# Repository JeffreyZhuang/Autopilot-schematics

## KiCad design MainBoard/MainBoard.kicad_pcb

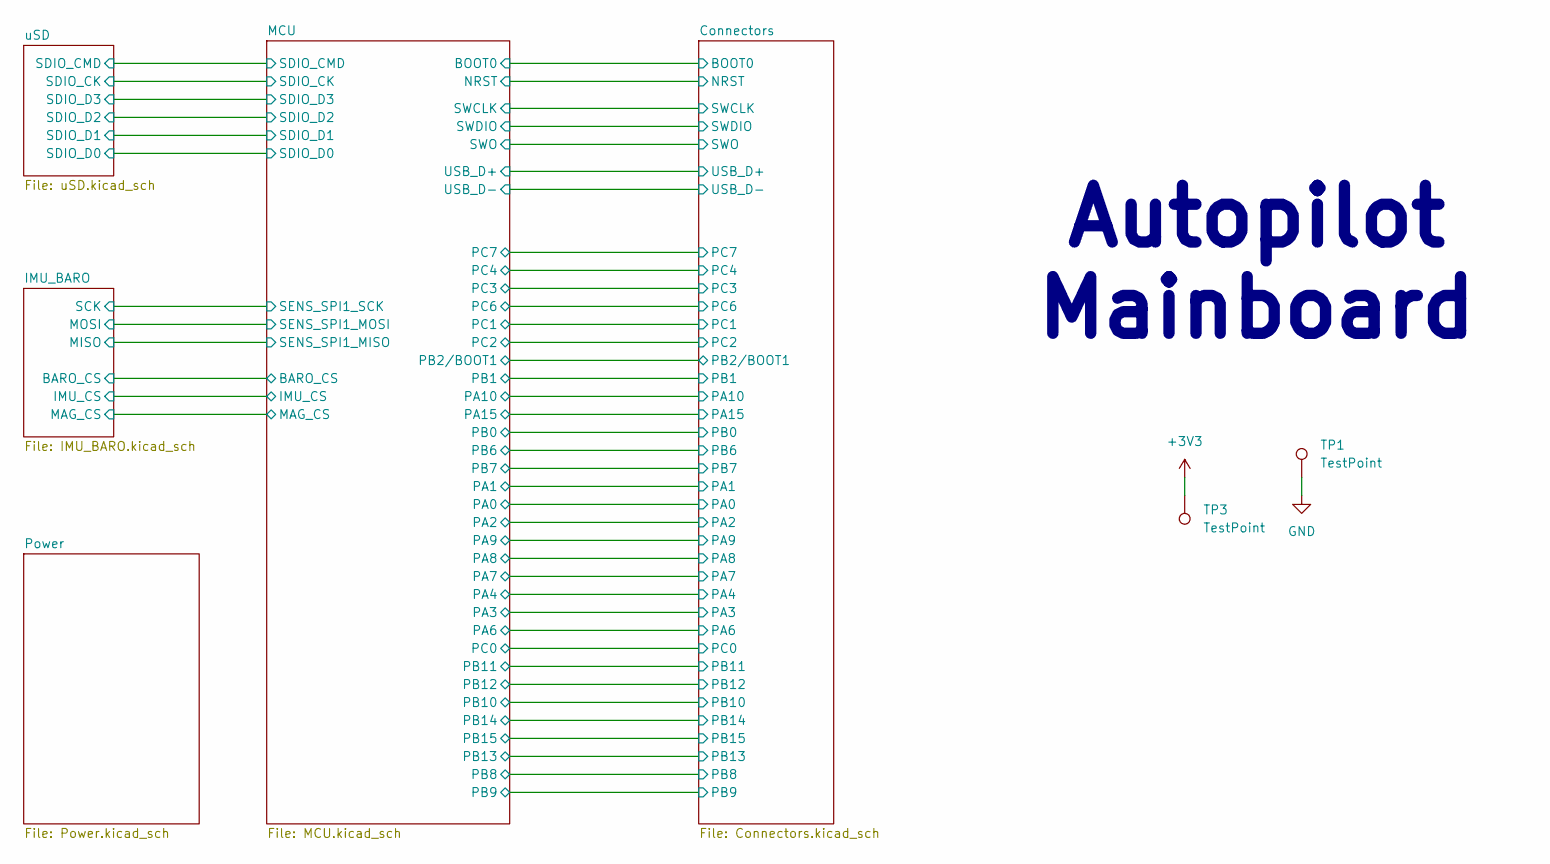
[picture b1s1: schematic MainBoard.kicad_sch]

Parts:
TP1: TestPoint; TestPoint_THTPad_D1.0mm_Drill0.5mm; LCSC Part # N/A
TP3: TestPoint; TestPoint_Pad_D1.0mm; LCSC Part # N/A

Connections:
+3V3: TP3.1; also elsewhere on the board
GND: TP1.1; also elsewhere on the board

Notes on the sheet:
Autopilot Mainboard

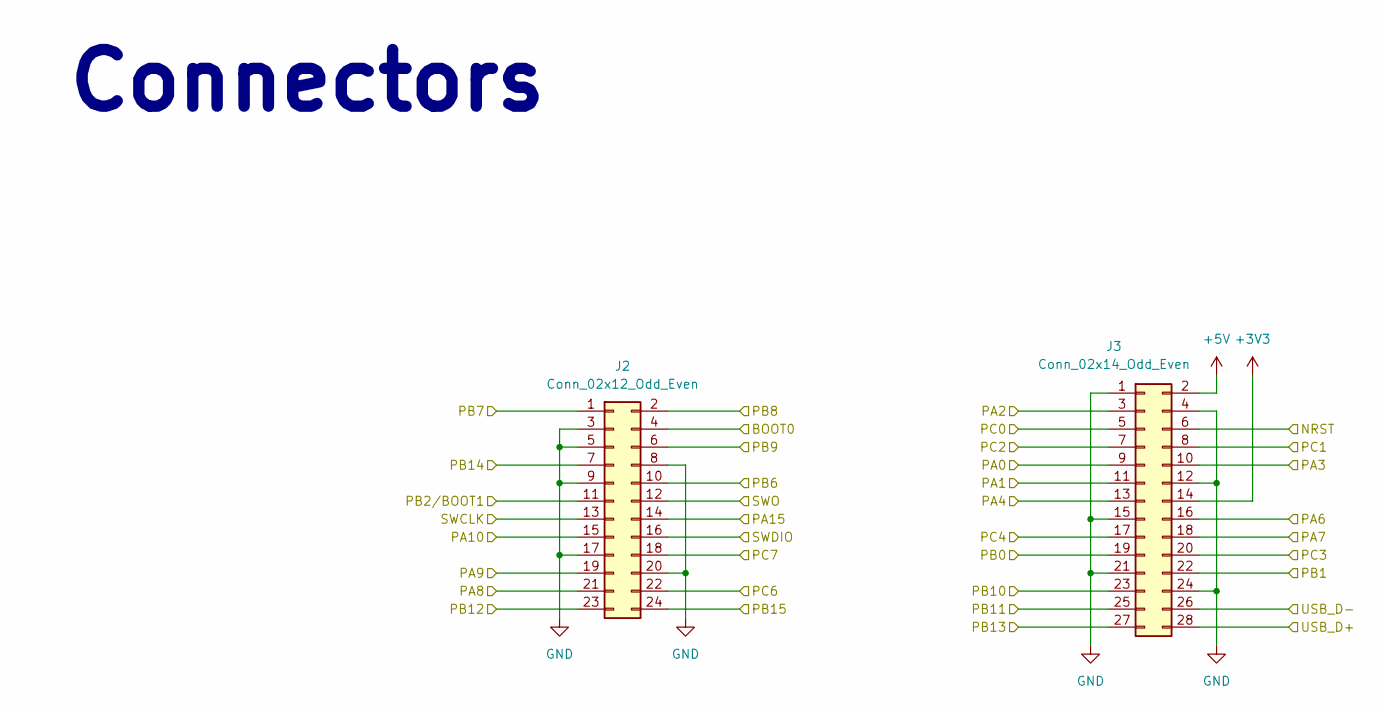
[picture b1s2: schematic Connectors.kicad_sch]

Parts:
J2: Conn_02x12_Odd_Even; PinHeader_2x12_P1.00mm_Vertical_SMD; LCSC Part # N/A
J3: Conn_02x14_Odd_Even; PinHeader_2x14_P1.00mm_Vertical_SMD; LCSC Part # N/A

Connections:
+3V3: J3.14; also elsewhere on the board
+5V: J3.2; also elsewhere on the board
/Connectors/BOOT0: J2.4; also elsewhere on the board
/Connectors/NRST: J3.6; also elsewhere on the board
/Connectors/PA0: J3.9; also elsewhere on the board
/Connectors/PA1: J3.11; also elsewhere on the board
/Connectors/PA2: J3.3; also elsewhere on the board
/Connectors/PA3: J3.10; also elsewhere on the board
/Connectors/PA4: J3.13; also elsewhere on the board
/Connectors/PA6: J3.16; also elsewhere on the board
/Connectors/PA7: J3.18; also elsewhere on the board
/Connectors/PA8: J2.21; also elsewhere on the board
/Connectors/PA9: J2.19; also elsewhere on the board
/Connectors/PA10: J2.15; also elsewhere on the board
/Connectors/PA15: J2.14; also elsewhere on the board
/Connectors/PB0: J3.19; also elsewhere on the board
/Connectors/PB1: J3.22; also elsewhere on the board
/Connectors/PB2/BOOT1: J2.11; also elsewhere on the board
/Connectors/PB6: J2.10; also elsewhere on the board
/Connectors/PB7: J2.1; also elsewhere on the board
/Connectors/PB8: J2.2; also elsewhere on the board
/Connectors/PB9: J2.6; also elsewhere on the board
/Connectors/PB10: J3.23; also elsewhere on the board
/Connectors/PB11: J3.25; also elsewhere on the board
/Connectors/PB12: J2.23; also elsewhere on the board
/Connectors/PB13: J3.27; also elsewhere on the board
/Connectors/PB14: J2.7; also elsewhere on the board
/Connectors/PB15: J2.24; also elsewhere on the board
/Connectors/PC0: J3.5; also elsewhere on the board
/Connectors/PC1: J3.8; also elsewhere on the board
/Connectors/PC2: J3.7; also elsewhere on the board
/Connectors/PC3: J3.20; also elsewhere on the board
/Connectors/PC4: J3.17; also elsewhere on the board
/Connectors/PC6: J2.22; also elsewhere on the board
/Connectors/PC7: J2.18; also elsewhere on the board
/Connectors/SWCLK: J2.13; also elsewhere on the board
/Connectors/SWDIO: J2.16; also elsewhere on the board
/Connectors/SWO: J2.12; also elsewhere on the board
/Connectors/USB_D+: J3.28; also elsewhere on the board
/Connectors/USB_D-: J3.26; also elsewhere on the board
GND: J2.3, J2.5, J2.8, J2.9, J2.17, J2.20, J3.1, J3.4, J3.12, J3.15, J3.21, J3.24; also elsewhere on the board

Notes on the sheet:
Connectors

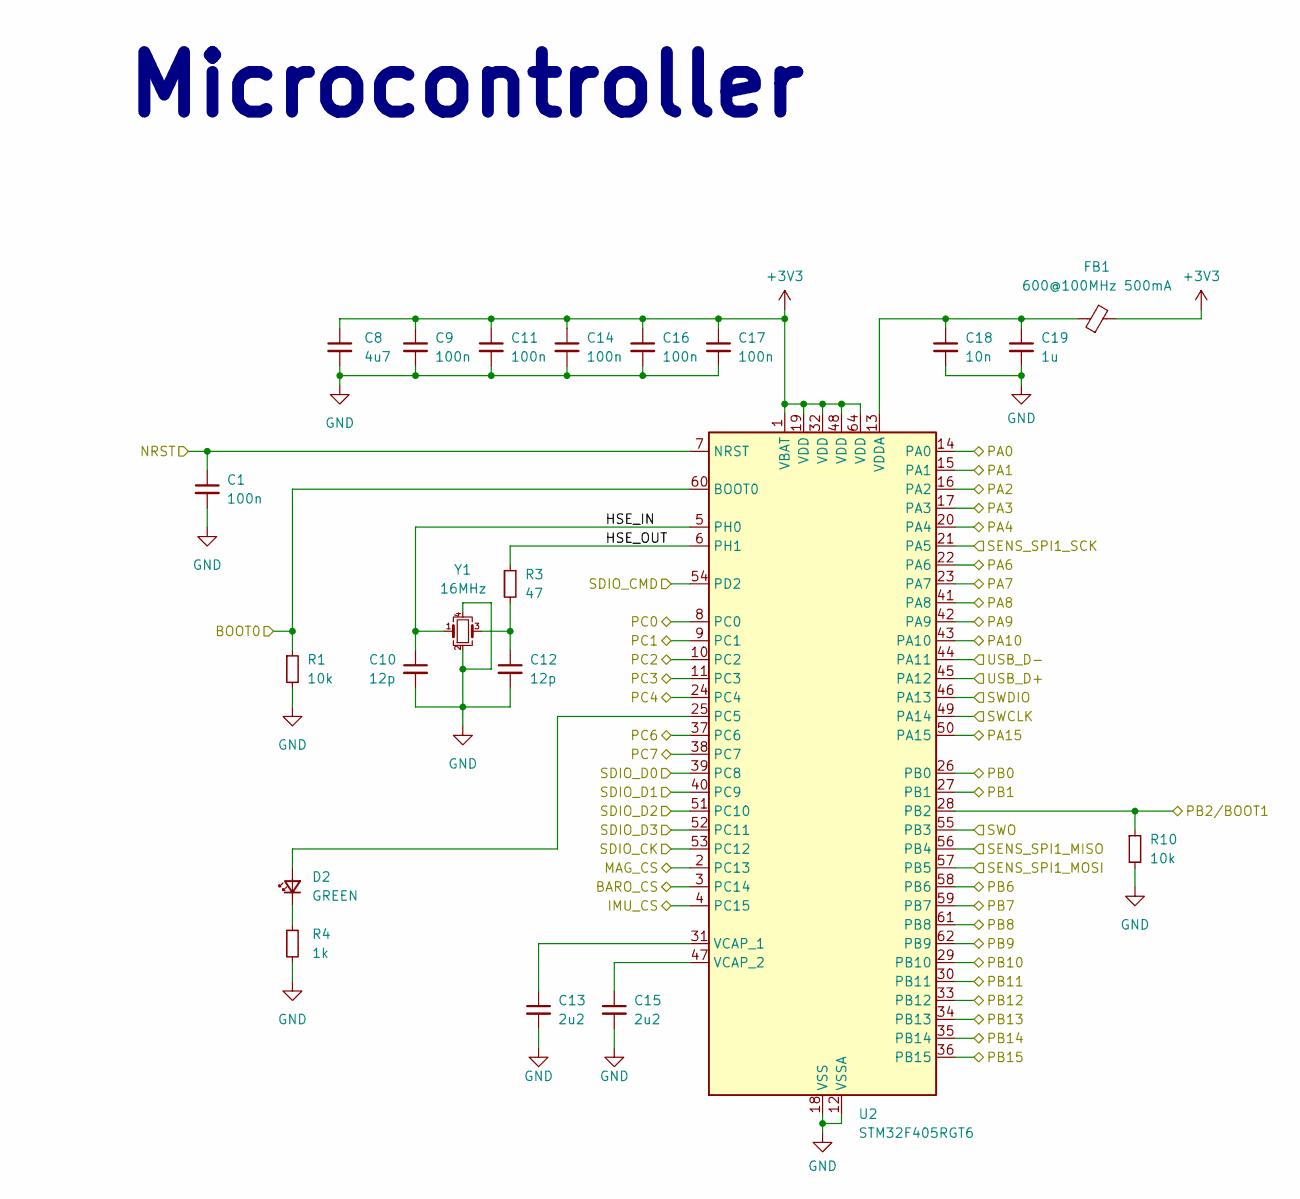
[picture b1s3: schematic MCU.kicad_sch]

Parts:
C1, C9, C11, C14, C16, C17: 100n; C_0402_1005Metric_Pad0.74x0.62mm_HandSolder; LCSC Part # N/A (C1525)
C8: 4u7; C_0402_1005Metric_Pad0.74x0.62mm_HandSolder; LCSC Part # N/A (C368809)
C10, C12: 12p; C_0402_1005Metric_Pad0.74x0.62mm_HandSolder; LCSC Part # N/A (C107034)
C13, C15: 2u2; C_0402_1005Metric_Pad0.74x0.62mm_HandSolder; LCSC Part # C170151
C18: 10n; C_0402_1005Metric_Pad0.74x0.62mm_HandSolder; LCSC Part # N/A (C15195)
C19: 1u; C_0402_1005Metric_Pad0.74x0.62mm_HandSolder; LCSC Part # N/A (C52923)
D2: GREEN; LED_0402_1005Metric_Pad0.77x0.64mm_HandSolder; LCSC Part # C130723
FB1: 600@100MHz 500mA; L_0805_2012Metric_Pad1.05x1.20mm_HandSolder; LCSC Part # N/A (C1017)
R1, R10: 10k; R_0402_1005Metric_Pad0.72x0.64mm_HandSolder; LCSC Part # N/A (C25744)
R3: 47; R_0402_1005Metric_Pad0.72x0.64mm_HandSolder; LCSC Part # N/A (C25118)
R4: 1k; R_0402_1005Metric_Pad0.72x0.64mm_HandSolder; LCSC Part # N/A (C11702)
U2: STM32F405RGT6; LQFP-64_10x10mm_P0.5mm; LCSC Part # C15742
Y1: 16MHz; Crystal_SMD_3225-4Pin_3.2x2.5mm; LCSC Part # N/A (C13738)

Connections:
+3V3: C8.1, C9.1, C11.1, C14.1, C16.1, C17.1, FB1.2, U2.1 (VBAT), U2.19 (VDD), U2.32 (VDD), U2.48 (VDD), U2.64 (VDD); also elsewhere on the board
/Connectors/BOOT0: R1.1, U2.60 (BOOT0); also elsewhere on the board
/Connectors/NRST: C1.1, U2.7 (NRST); also elsewhere on the board
/Connectors/PA0: U2.14 (PA0); also elsewhere on the board
/Connectors/PA1: U2.15 (PA1); also elsewhere on the board
/Connectors/PA2: U2.16 (PA2); also elsewhere on the board
/Connectors/PA3: U2.17 (PA3); also elsewhere on the board
/Connectors/PA4: U2.20 (PA4); also elsewhere on the board
/Connectors/PA6: U2.22 (PA6); also elsewhere on the board
/Connectors/PA7: U2.23 (PA7); also elsewhere on the board
/Connectors/PA8: U2.41 (PA8); also elsewhere on the board
/Connectors/PA9: U2.42 (PA9); also elsewhere on the board
/Connectors/PA10: U2.43 (PA10); also elsewhere on the board
/Connectors/PA15: U2.50 (PA15); also elsewhere on the board
/Connectors/PB0: U2.26 (PB0); also elsewhere on the board
/Connectors/PB1: U2.27 (PB1); also elsewhere on the board
/Connectors/PB2/BOOT1: R10.1, U2.28 (PB2); also elsewhere on the board
/Connectors/PB6: U2.58 (PB6); also elsewhere on the board
/Connectors/PB7: U2.59 (PB7); also elsewhere on the board
/Connectors/PB8: U2.61 (PB8); also elsewhere on the board
/Connectors/PB9: U2.62 (PB9); also elsewhere on the board
/Connectors/PB10: U2.29 (PB10); also elsewhere on the board
/Connectors/PB11: U2.30 (PB11); also elsewhere on the board
/Connectors/PB12: U2.33 (PB12); also elsewhere on the board
/Connectors/PB13: U2.34 (PB13); also elsewhere on the board
/Connectors/PB14: U2.35 (PB14); also elsewhere on the board
/Connectors/PB15: U2.36 (PB15); also elsewhere on the board
/Connectors/PC0: U2.8 (PC0); also elsewhere on the board
/Connectors/PC1: U2.9 (PC1); also elsewhere on the board
/Connectors/PC2: U2.10 (PC2); also elsewhere on the board
/Connectors/PC3: U2.11 (PC3); also elsewhere on the board
/Connectors/PC4: U2.24 (PC4); also elsewhere on the board
/Connectors/PC6: U2.37 (PC6); also elsewhere on the board
/Connectors/PC7: U2.38 (PC7); also elsewhere on the board
/Connectors/SWCLK: U2.49 (PA14); also elsewhere on the board
/Connectors/SWDIO: U2.46 (PA13); also elsewhere on the board
/Connectors/SWO: U2.55 (PB3); also elsewhere on the board
/Connectors/USB_D+: U2.45 (PA12); also elsewhere on the board
/Connectors/USB_D-: U2.44 (PA11); also elsewhere on the board
/IMU_BARO/BARO_CS: U2.3 (PC14); also elsewhere on the board
/IMU_BARO/IMU_CS: U2.4 (PC15); also elsewhere on the board
/IMU_BARO/MAG_CS: U2.2 (PC13); also elsewhere on the board
/IMU_BARO/MISO: U2.56 (PB4); also elsewhere on the board
/IMU_BARO/MOSI: U2.57 (PB5); also elsewhere on the board
/IMU_BARO/SCK: U2.21 (PA5); also elsewhere on the board
/MCU/HSE_IN: C10.1, U2.5 (PH0), Y1.1
/MCU/HSE_OUT: R3.1, U2.6 (PH1)
/MCU/SDIO_CK: U2.53 (PC12); also elsewhere on the board
/MCU/SDIO_CMD: U2.54 (PD2); also elsewhere on the board
/MCU/SDIO_D0: U2.39 (PC8); also elsewhere on the board
/MCU/SDIO_D1: U2.40 (PC9); also elsewhere on the board
/MCU/SDIO_D2: U2.51 (PC10); also elsewhere on the board
/MCU/SDIO_D3: U2.52 (PC11); also elsewhere on the board
GND: C1.2, C8.2, C9.2, C10.2, C11.2, C12.2, C13.2, C14.2, C15.2, C16.2, C17.2, C18.2, C19.2, R1.2, R4.2, R10.2, U2.12 (VSSA), U2.18 (VSS), U2.63 (VSS), Y1.2, Y1.4; also elsewhere on the board
unnamed: C12.1, R3.2, Y1.3
unnamed: D2.2 (A), U2.25 (PC5)
unnamed: D2.1 (K), R4.1
unnamed: C13.1, U2.31 (VCAP_1)
unnamed: C15.1, U2.47 (VCAP_2)
unnamed: C18.1, C19.1, FB1.1, U2.13 (VDDA)

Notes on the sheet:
Microcontroller

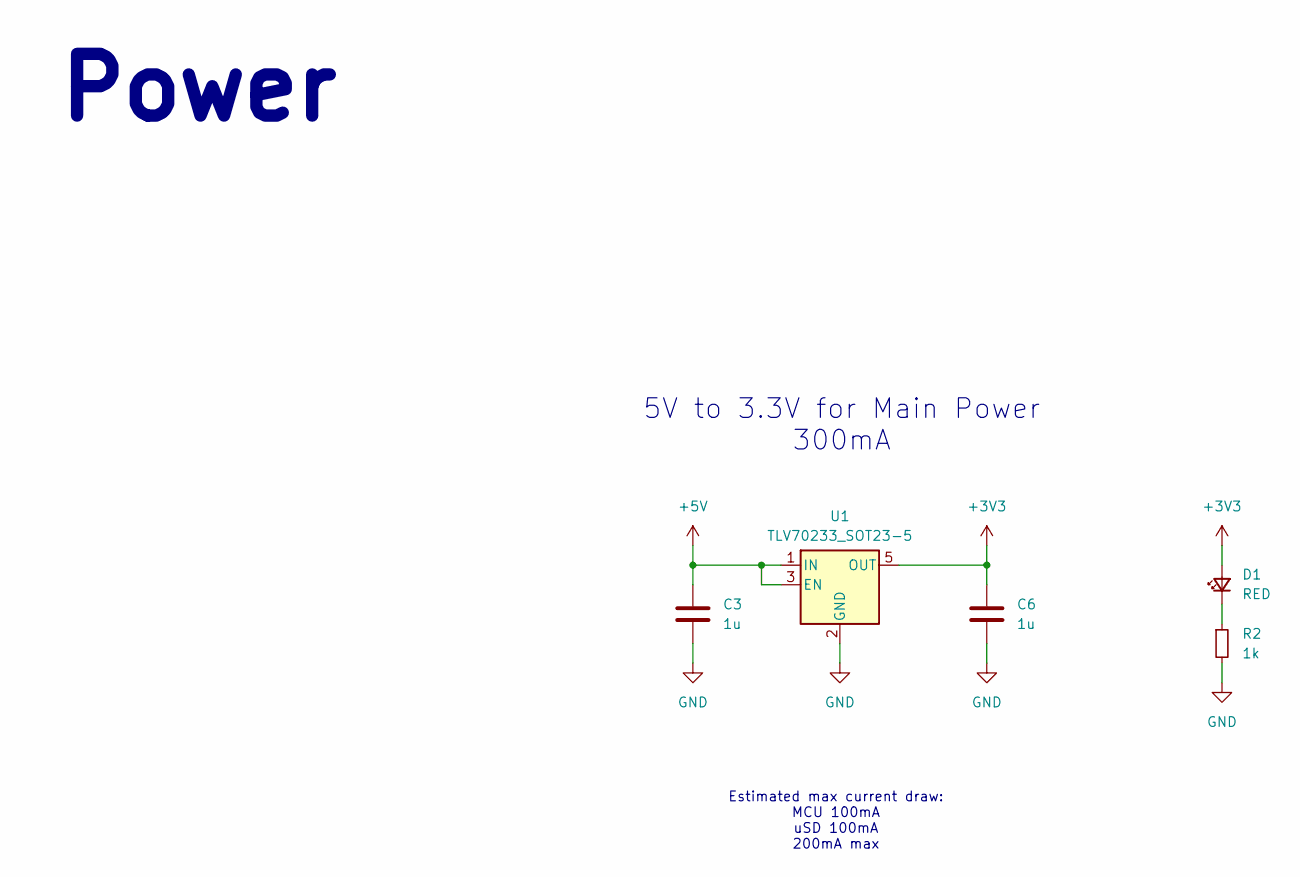
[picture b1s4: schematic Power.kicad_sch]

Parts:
C3, C6: 1u; C_0402_1005Metric_Pad0.74x0.62mm_HandSolder; LCSC Part # N/A (C52923)
D1: RED; LED_0402_1005Metric_Pad0.77x0.64mm_HandSolder; LCSC Part # N/A (C130719)
R2: 1k; R_0402_1005Metric_Pad0.72x0.64mm_HandSolder; LCSC Part # N/A (C11702)
U1: TLV70233_SOT23-5; SOT-23-5; LCSC Part # C26833

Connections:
+3V3: C6.1, D1.2 (A), U1.5 (OUT); also elsewhere on the board
+5V: C3.1, U1.1 (IN), U1.3 (EN); also elsewhere on the board
GND: C3.2, C6.2, R2.2, U1.2 (GND); also elsewhere on the board
unnamed: D1.1 (K), R2.1

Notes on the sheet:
5V to 3.3V for Main Power 300mA
Estimated max current draw: MCU 100mA uSD 100mA 200mA max
Power

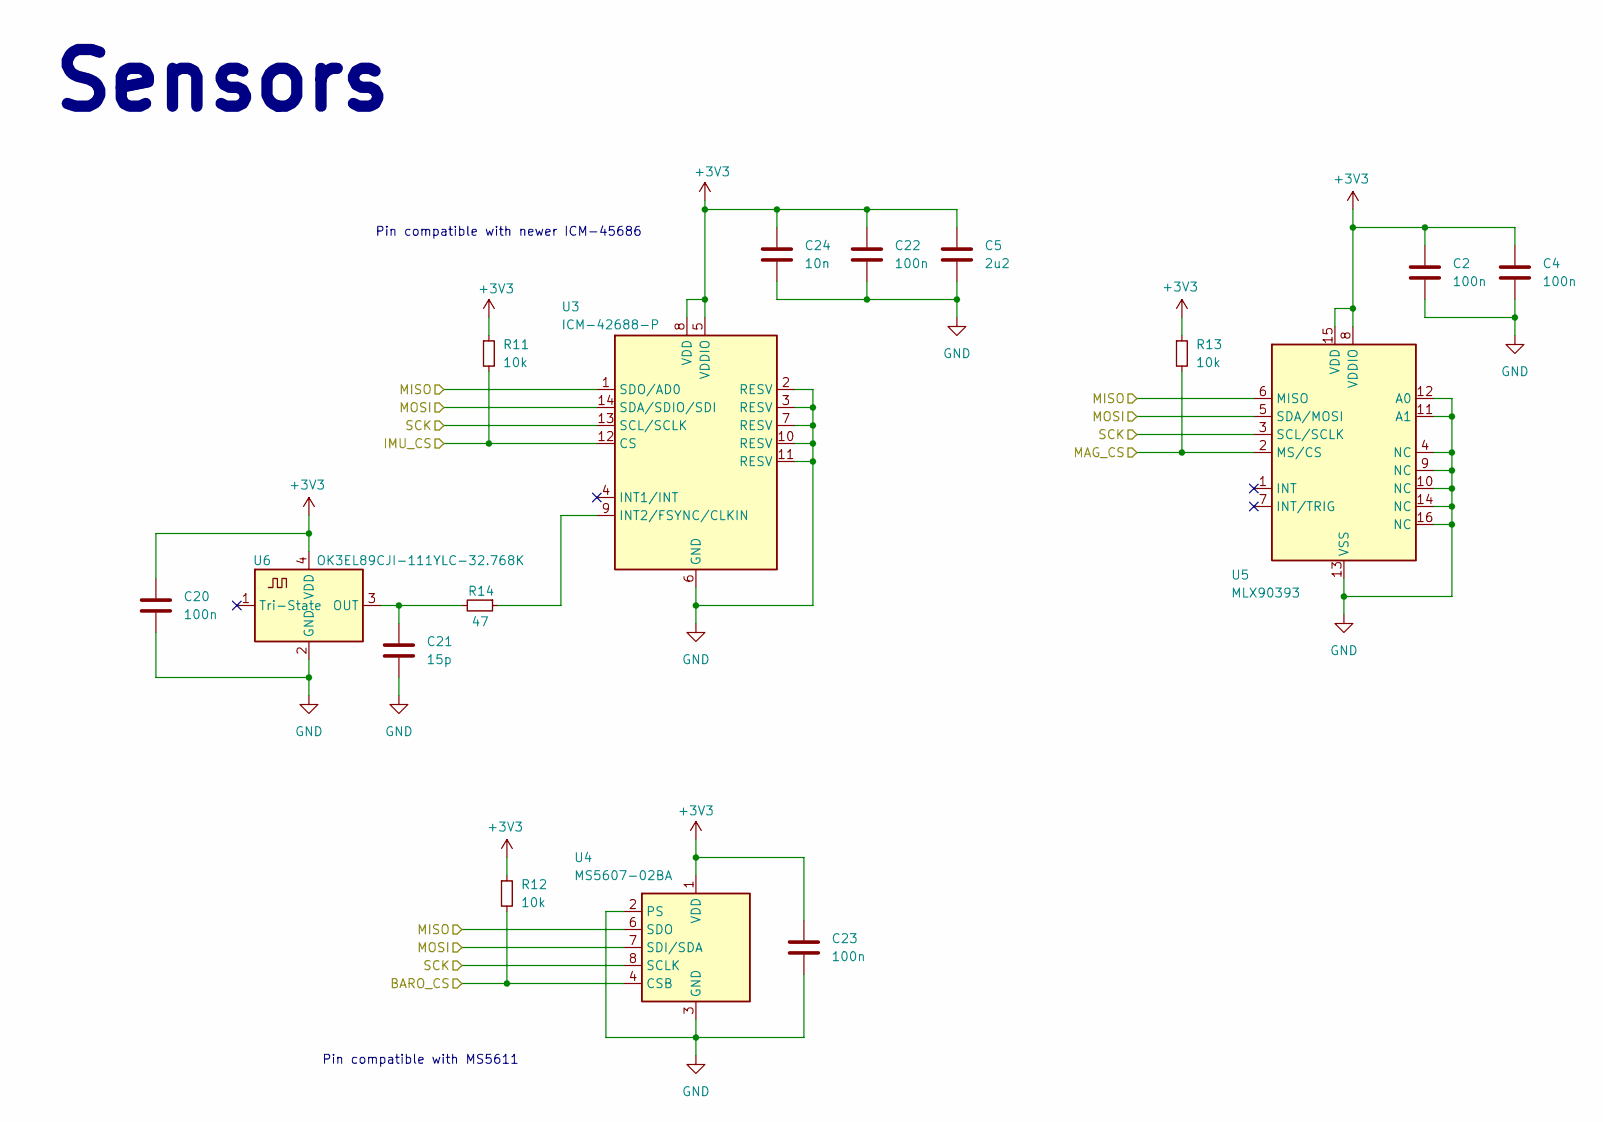
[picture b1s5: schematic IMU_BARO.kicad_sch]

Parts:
C2, C4, C20, C22, C23: 100n; C_0402_1005Metric_Pad0.74x0.62mm_HandSolder; LCSC Part # N/A (C1525)
C5: 2u2; C_0402_1005Metric_Pad0.74x0.62mm_HandSolder; LCSC Part # C170151
C21: 15p; C_0402_1005Metric_Pad0.74x0.62mm_HandSolder; LCSC Part # C1548
C24: 10n; C_0402_1005Metric_Pad0.74x0.62mm_HandSolder; LCSC Part # N/A (C15195)
R11, R12, R13: 10k; R_0402_1005Metric_Pad0.72x0.64mm_HandSolder; LCSC Part # N/A (C25744)
R14: 47; R_0402_1005Metric_Pad0.72x0.64mm_HandSolder; LCSC Part # N/A (C25118)
U3: ICM-42688-P; Bosch_LGA-14_3x2.5mm_P0.5mm; LCSC Part # C1850418
U4: MS5607-02BA; LGA-8_3x5mm_P1.25mm; LCSC Part # N/A (C97627)
U5: MLX90393; MLX90393_Handsolder; LCSC Part # C2654971
U6: OK3EL89CJI-111YLC-32.768K; Crystal_SMD_2520-4Pin_2.5x2.0mm; LCSC Part # C7425456

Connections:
+3V3: C2.1, C4.1, C5.1, C20.1, C22.1, C23.1, C24.1, R11.1, R12.1, R13.1, U3.5 (VDDIO), U3.8 (VDD), U4.1 (VDD), U5.8 (VDDIO), U5.15 (VDD), U6.4 (VDD); also elsewhere on the board
/IMU_BARO/BARO_CS: R12.2, U4.4 (CSB), U4.5 (CSB); also elsewhere on the board
/IMU_BARO/IMU_CS: R11.2, U3.12 (CS); also elsewhere on the board
/IMU_BARO/MAG_CS: R13.2, U5.2 (MS/CS); also elsewhere on the board
/IMU_BARO/MISO: U3.1 (SDO/AD0), U4.6 (SDO), U5.6 (MISO); also elsewhere on the board
/IMU_BARO/MOSI: U3.14 (SDA/SDIO/SDI), U4.7 (SDI/SDA), U5.5 (SDA/MOSI); also elsewhere on the board
/IMU_BARO/SCK: U3.13 (SCL/SCLK), U4.8 (SCLK), U5.3 (SCL/SCLK); also elsewhere on the board
GND: C2.2, C4.2, C5.2, C20.2, C21.2, C22.2, C23.2, C24.2, U3.2 (RESV), U3.3 (RESV), U3.6 (GND), U3.7 (RESV), U3.10 (RESV), U3.11 (RESV), U4.2 (PS), U4.3 (GND), U5.4 (NC), U5.9 (NC), U5.10 (NC), U5.11 (A1), U5.12 (A0), U5.13 (VSS), U5.14 (NC), U5.16 (NC), U6.2 (GND); also elsewhere on the board
unnamed: R14.1, U3.9 (INT2/FSYNC/CLKIN)
unnamed: C21.1, R14.2, U6.3 (OUT)

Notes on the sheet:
Sensors
Pin compatible with MS5611
Pin compatible with newer ICM-45686

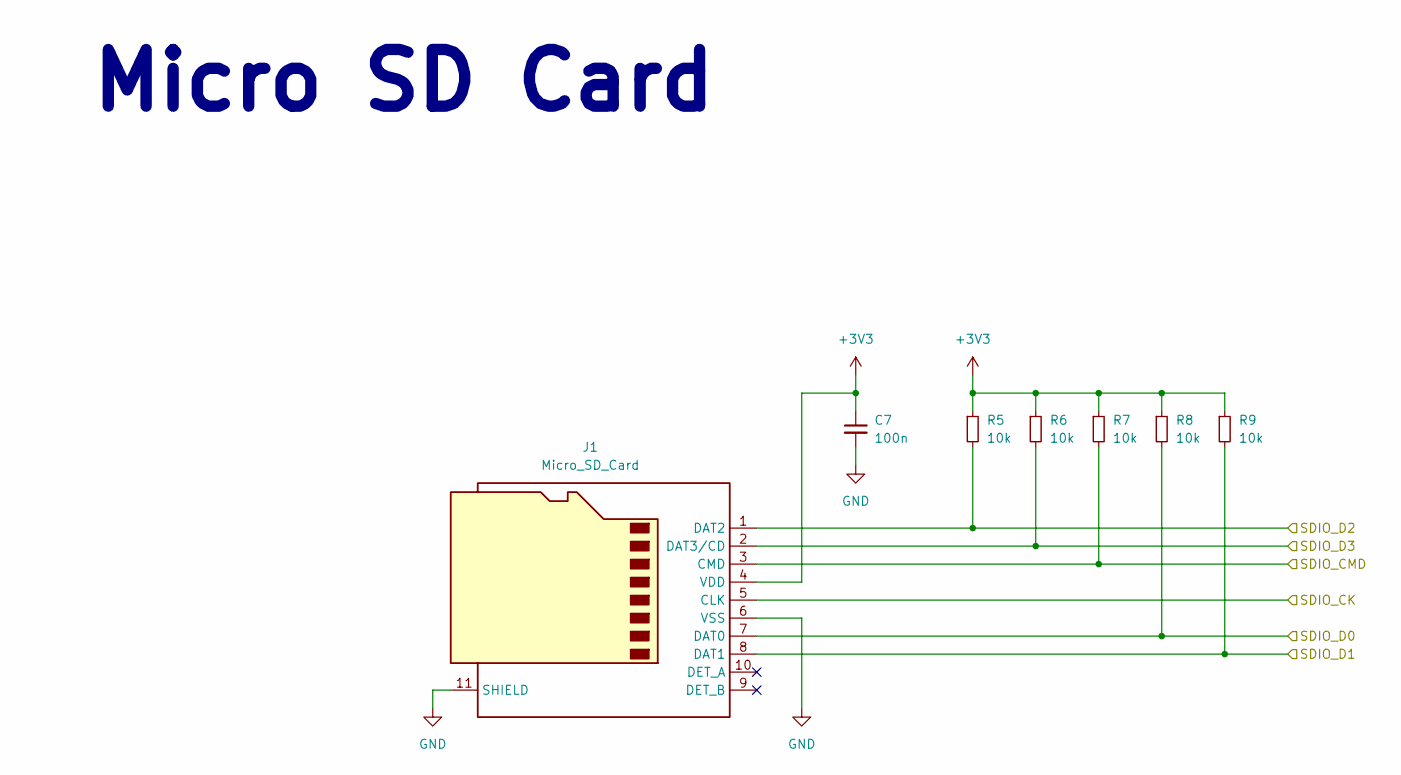
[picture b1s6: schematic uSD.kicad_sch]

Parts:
C7: 100n; C_0402_1005Metric_Pad0.74x0.62mm_HandSolder; LCSC Part # N/A (C1525)
J1: Micro_SD_Card; microSD_HC_Molex_104031-0811; LCSC Part # C585350
R5, R6, R7, R8, R9: 10k; R_0402_1005Metric_Pad0.72x0.64mm_HandSolder; LCSC Part # N/A (C25744)

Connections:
+3V3: C7.1, J1.4 (VDD), R5.1, R6.1, R7.1, R8.1, R9.1; also elsewhere on the board
/MCU/SDIO_CK: J1.5 (CLK); also elsewhere on the board
/MCU/SDIO_CMD: J1.3 (CMD), R7.2; also elsewhere on the board
/MCU/SDIO_D0: J1.7 (DAT0), R8.2; also elsewhere on the board
/MCU/SDIO_D1: J1.8 (DAT1), R9.2; also elsewhere on the board
/MCU/SDIO_D2: J1.1 (DAT2), R5.2; also elsewhere on the board
/MCU/SDIO_D3: J1.2 (DAT3/CD), R6.2; also elsewhere on the board
GND: C7.2, J1.6 (VSS), J1.11 (SHIELD); also elsewhere on the board

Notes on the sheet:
Micro SD Card

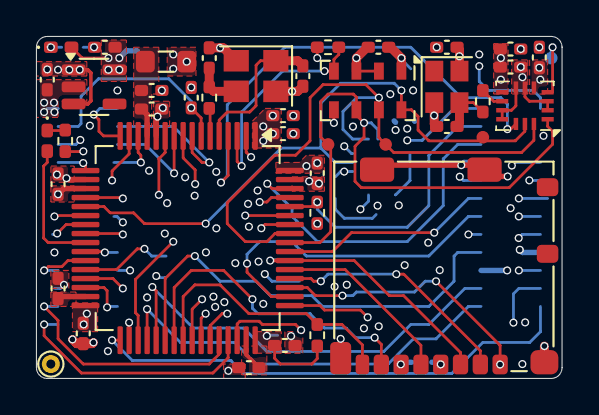
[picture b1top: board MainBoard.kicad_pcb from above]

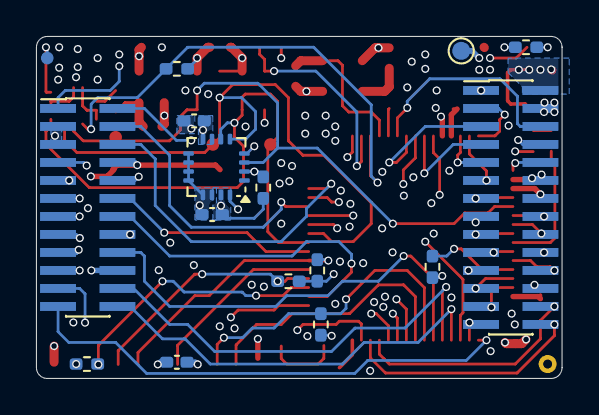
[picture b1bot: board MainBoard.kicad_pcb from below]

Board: 6 copper layers, 29.2 x 19.0 mm, 53 parts (15 on the bottom side), 64 nets.

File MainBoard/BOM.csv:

"Reference","Value","Footprint","Qty","LCSC Part #"
"C1,C2,C4,C7,C9,C11,C14,C16,C17,C20,C22,C23","100n","Capacitor_SMD:C_0402_1005Metric_Pad0.74x0.62mm_HandSolder","12","N/A (C1525)"
"C3,C6,C19","1u","Capacitor_SMD:C_0402_1005Metric_Pad0.74x0.62mm_HandSolder","3","N/A (C52923)"
"C5,C13,C15","2u2","Capacitor_SMD:C_0402_1005Metric_Pad0.74x0.62mm_HandSolder","3","C170151"
"C8","4u7","Capacitor_SMD:C_0402_1005Metric_Pad0.74x0.62mm_HandSolder","1","N/A (C368809)"
"C10,C12","12p","Capacitor_SMD:C_0402_1005Metric_Pad0.74x0.62mm_HandSolder","2","N/A (C107034)"
"C18,C24","10n","Capacitor_SMD:C_0402_1005Metric_Pad0.74x0.62mm_HandSolder","2","N/A (C15195)"
"C21","15p","Capacitor_SMD:C_0402_1005Metric_Pad0.74x0.62mm_HandSolder","1","C1548"
"D1","RED","LED_SMD:LED_0402_1005Metric_Pad0.77x0.64mm_HandSolder","1","N/A (C130719)"
"D2","GREEN","LED_SMD:LED_0402_1005Metric_Pad0.77x0.64mm_HandSolder","1","C130723"
"FB1","600@100MHz 500mA","Inductor_SMD:L_0805_2012Metric_Pad1.05x1.20mm_HandSolder","1","N/A (C1017)"
"J1","Micro_SD_Card","Global_Library:microSD_HC_Molex_104031-0811","1","C585350"
"J2","Conn_02x12_Odd_Even","Connector_PinHeader_1.00mm:PinHeader_2x12_P1.00mm_Vertical_SMD","1","N/A"
"J3","Conn_02x14_Odd_Even","Connector_PinHeader_1.00mm:PinHeader_2x14_P1.00mm_Vertical_SMD","1","N/A"
"R1,R5,R6,R7,R8,R9,R10,R11,R12,R13","10k","Resistor_SMD:R_0402_1005Metric_Pad0.72x0.64mm_HandSolder","10","N/A (C25744)"
"R2,R4","1k","Resistor_SMD:R_0402_1005Metric_Pad0.72x0.64mm_HandSolder","2","N/A (C11702)"
"R3,R14","47","Resistor_SMD:R_0402_1005Metric_Pad0.72x0.64mm_HandSolder","2","N/A (C25118)"
"TP1,TP3","TestPoint","-- mixed values --","2","N/A"
"U1","TLV70233_SOT23-5","Package_TO_SOT_SMD:SOT-23-5","1","C26833"
"U2","STM32F405RGT6","Package_QFP:LQFP-64_10x10mm_P0.5mm","1","C15742"
"U3","ICM-42688-P","Package_LGA:Bosch_LGA-14_3x2.5mm_P0.5mm","1","C1850418"
"U4","MS5607-02BA","Package_LGA:LGA-8_3x5mm_P1.25mm","1","N/A (C97627)"
"U5","MLX90393","Global_Library:MLX90393_Handsolder","1","C2654971"
"U6","OK3EL89CJI-111YLC-32.768K","Crystal:Crystal_SMD_2520-4Pin_2.5x2.0mm","1","C7425456"
"Y1","16MHz","Crystal:Crystal_SMD_3225-4Pin_3.2x2.5mm","1","N/A (C13738)"

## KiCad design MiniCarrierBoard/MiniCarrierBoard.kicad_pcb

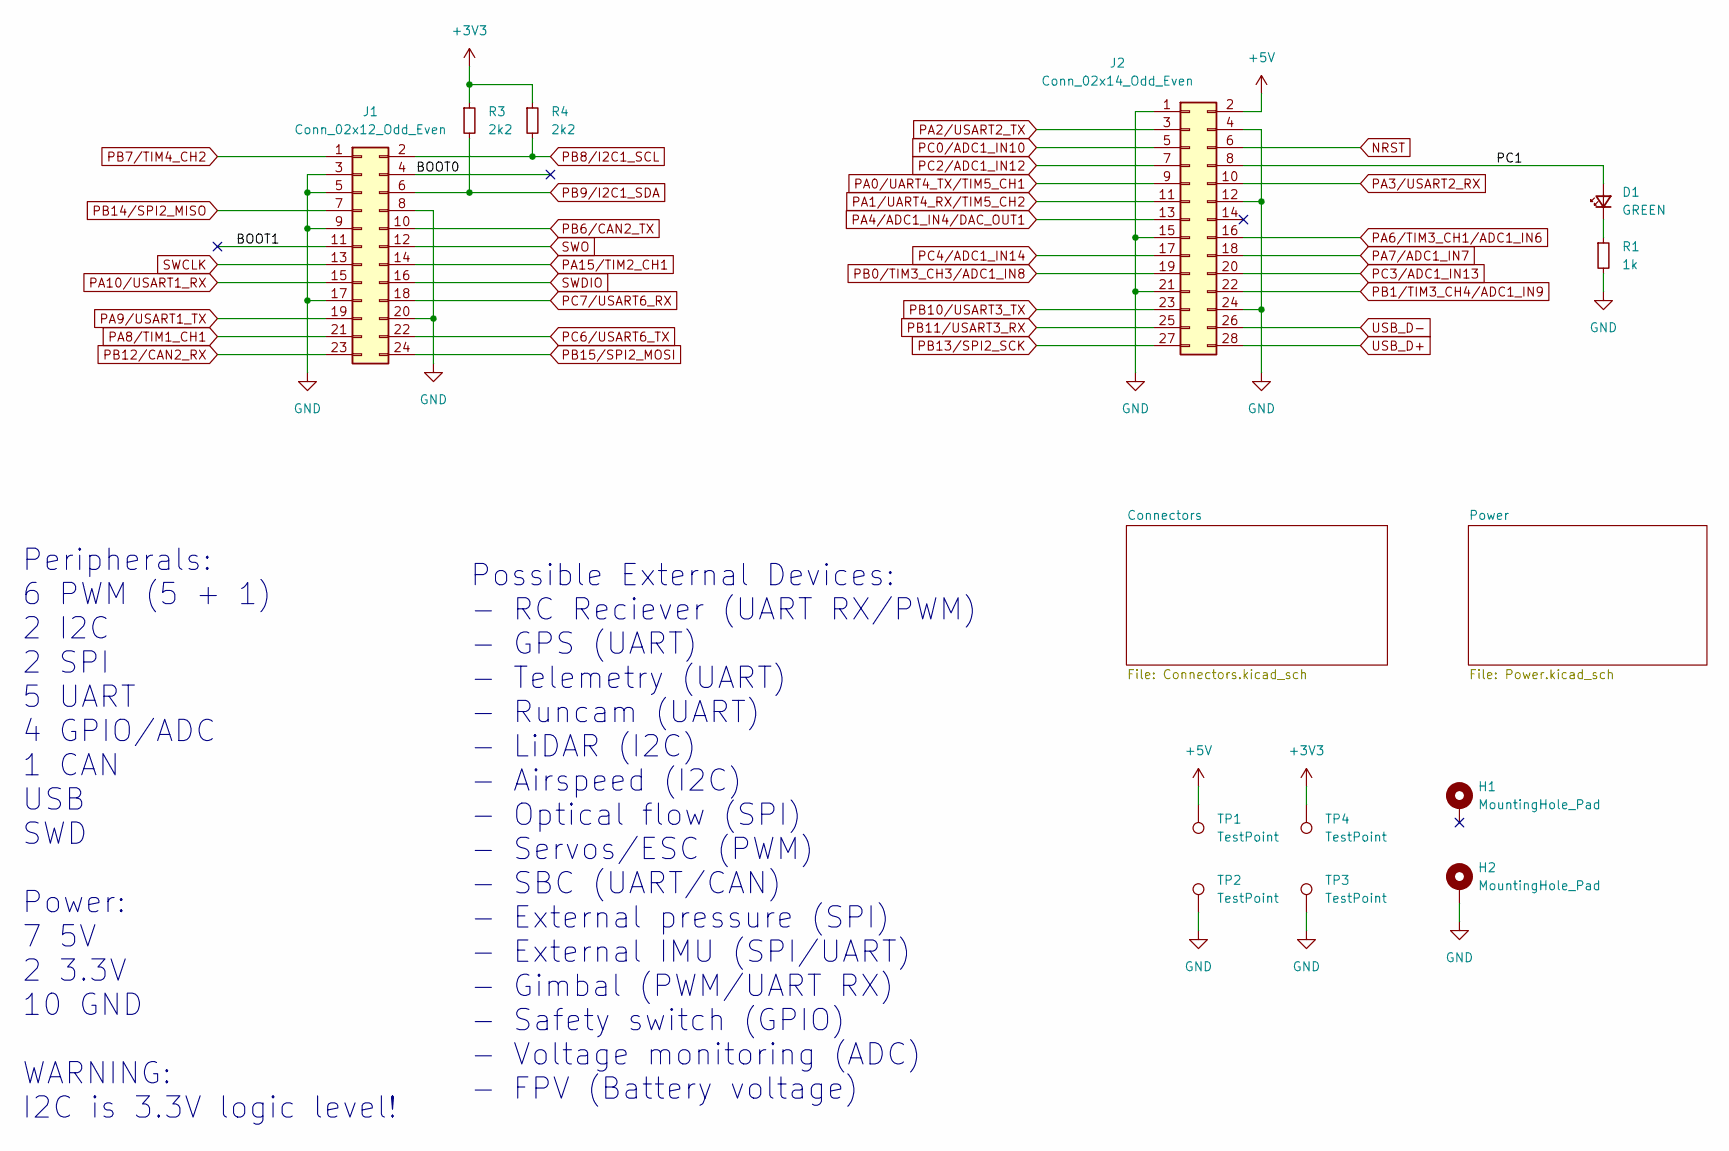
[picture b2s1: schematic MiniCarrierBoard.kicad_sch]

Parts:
D1: GREEN; LED_0402_1005Metric_Pad0.77x0.64mm_HandSolder; LCSC Part # C130723
H1, H2: MountingHole_Pad; MountingHole_2.2mm_M2_ISO7380_Pad; LCSC Part # N/A
J1: Conn_02x12_Odd_Even; PinSocket_2x12_P1.00mm_Vertical_SMD; LCSC Part # N/A
J2: Conn_02x14_Odd_Even; PinSocket_2x14_P1.00mm_Vertical_SMD; LCSC Part # N/A
R1: 1k; R_0402_1005Metric_Pad0.72x0.64mm_HandSolder; LCSC Part # N/A (C11702)
R3, R4: 2k2; R_0402_1005Metric_Pad0.72x0.64mm_HandSolder; LCSC Part # N/A (C25879)
TP1, TP2, TP3, TP4: TestPoint; TestPoint_Pad_D1.0mm; LCSC Part # N/A

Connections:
+3V3: R3.1, R4.1, TP4.1; also elsewhere on the board
+5V: J2.2, TP1.1; also elsewhere on the board
/BOOT0: J1.4
/BOOT1: J1.11
/PC1: D1.2 (A), J2.8
GND: H2.1, J1.3, J1.5, J1.8, J1.9, J1.17, J1.20, J2.1, J2.4, J2.12, J2.15, J2.21, J2.24, R1.2, TP2.1, TP3.1; also elsewhere on the board
NRST: J2.6; also elsewhere on the board
unnamed: D1.1 (K), R1.1
PA0/UART4_TX/TIM5_CH1: J2.9; also elsewhere on the board
PA1/UART4_RX/TIM5_CH2: J2.11; also elsewhere on the board
PA2/USART2_TX: J2.3; also elsewhere on the board
PA3/USART2_RX: J2.10; also elsewhere on the board
PA4/ADC1_IN4/DAC_OUT1: J2.13; also elsewhere on the board
PA6/TIM3_CH1/ADC1_IN6: J2.16; also elsewhere on the board
PA7/ADC1_IN7: J2.18; also elsewhere on the board
PA8/TIM1_CH1: J1.21; also elsewhere on the board
PA9/USART1_TX: J1.19; also elsewhere on the board
PA10/USART1_RX: J1.15; also elsewhere on the board
PA15/TIM2_CH1: J1.14; also elsewhere on the board
PB0/TIM3_CH3/ADC1_IN8: J2.19; also elsewhere on the board
PB1/TIM3_CH4/ADC1_IN9: J2.22; also elsewhere on the board
PB6/CAN2_TX: J1.10; also elsewhere on the board
PB7/TIM4_CH2: J1.1; also elsewhere on the board
PB8/I2C1_SCL: J1.2, R4.2; also elsewhere on the board
PB9/I2C1_SDA: J1.6, R3.2; also elsewhere on the board
PB10/USART3_TX: J2.23; also elsewhere on the board
PB11/USART3_RX: J2.25; also elsewhere on the board
PB12/CAN2_RX: J1.23; also elsewhere on the board
PB13/SPI2_SCK: J2.27; also elsewhere on the board
PB14/SPI2_MISO: J1.7; also elsewhere on the board
PB15/SPI2_MOSI: J1.24; also elsewhere on the board
PC0/ADC1_IN10: J2.5; also elsewhere on the board
PC2/ADC1_IN12: J2.7; also elsewhere on the board
PC3/ADC1_IN13: J2.20; also elsewhere on the board
PC4/ADC1_IN14: J2.17; also elsewhere on the board
PC6/USART6_TX: J1.22; also elsewhere on the board
PC7/USART6_RX: J1.18; also elsewhere on the board
SWCLK: J1.13; also elsewhere on the board
SWDIO: J1.16; also elsewhere on the board
SWO: J1.12; also elsewhere on the board
USB_D+: J2.28; also elsewhere on the board
USB_D-: J2.26; also elsewhere on the board

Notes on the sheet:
Peripherals: 6 PWM (5 + 1) 2 I2C 2 SPI 5 UART 4 GPIO/ADC 1 CAN USB SWD Power: 7 5V 2 3.3V 10 GND WARNING: I2C is 3.3V logic level!
Possible External Devices: - RC Reciever (UART RX/PWM) - GPS (UART) - Telemetry (UART) - Runcam (UART) - LiDAR (I2C) - Airspeed (I2C) - Optical flow (SPI) - Servos/ESC (PWM) - SBC (UART/CAN) - External pressure (SPI) - External IMU (SPI/UART) - Gimbal (PWM/UART RX) - Safety switch (GPIO) - Voltage 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

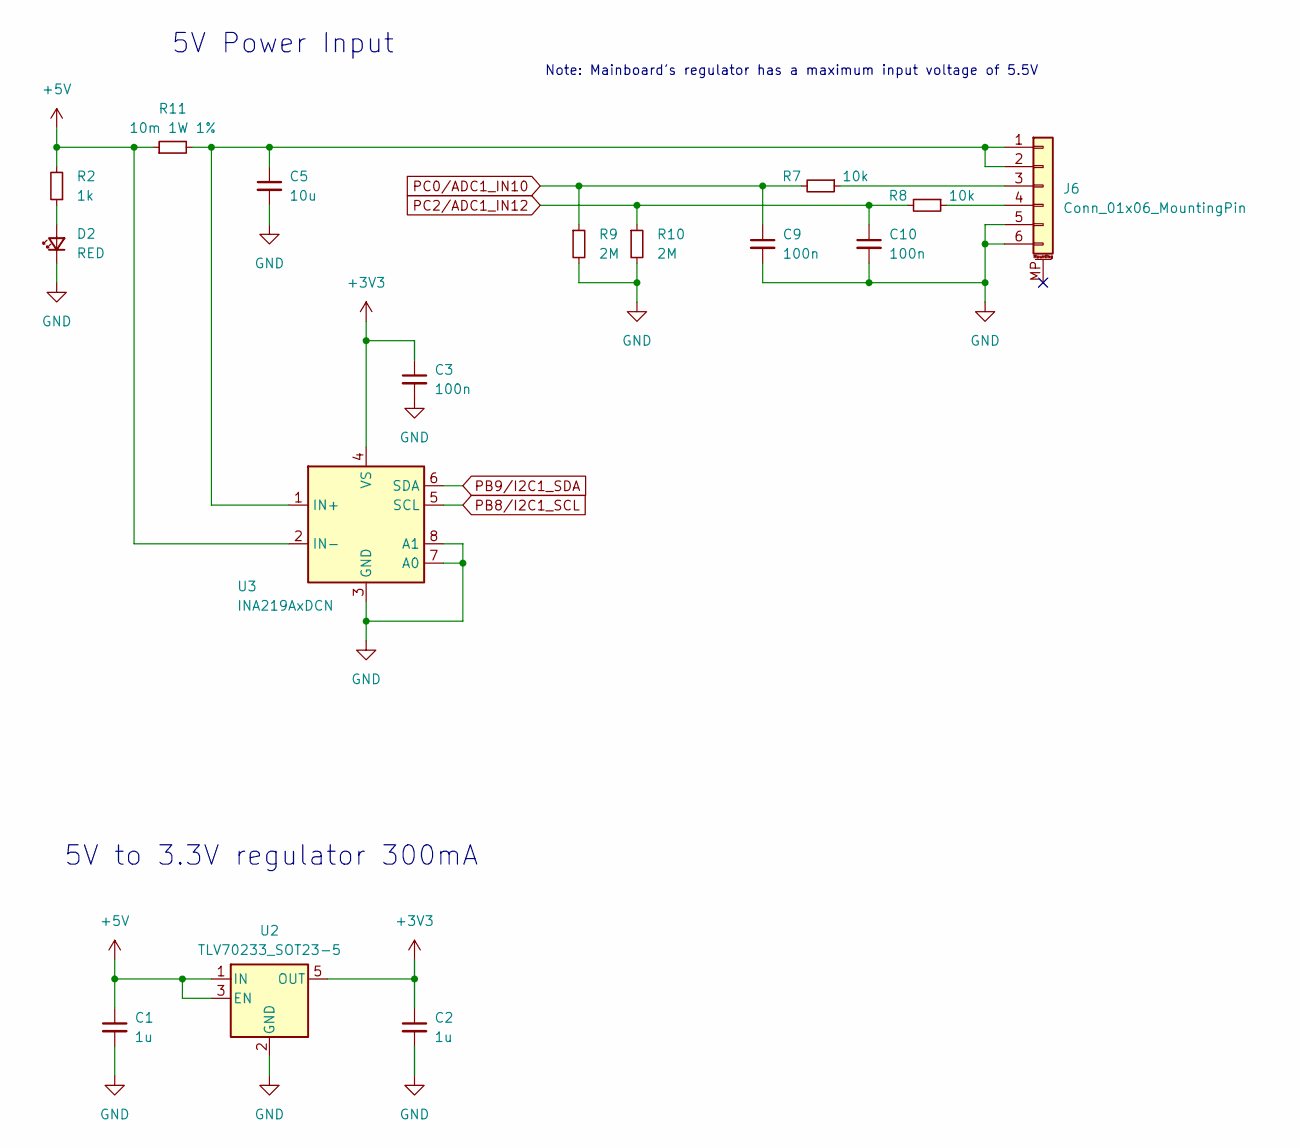
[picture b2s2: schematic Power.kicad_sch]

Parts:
C1, C2: 1u; C_0402_1005Metric_Pad0.74x0.62mm_HandSolder; LCSC Part # N/A (C2959727)
C3, C9, C10: 100n; C_0402_1005Metric_Pad0.74x0.62mm_HandSolder; LCSC Part # N/A (C1525)
C5: 10u; C_0805_2012Metric_Pad1.18x1.45mm_HandSolder; LCSC Part # N/A (C15850)
D2: RED; LED_0402_1005Metric_Pad0.77x0.64mm_HandSolder; LCSC Part # N/A (C130719)
J6: Conn_01x06_MountingPin; JST_GH_BM06B-GHS-TBT_1x06-1MP_P1.25mm_Vertical; LCSC Part # C189892
R2: 1k; R_0402_1005Metric_Pad0.72x0.64mm_HandSolder; LCSC Part # N/A (C11702)
R7, R8: 10k; R_0402_1005Metric_Pad0.72x0.64mm_HandSolder; LCSC Part # N/A (C25744)
R9, R10: 2M; R_0402_1005Metric_Pad0.72x0.64mm_HandSolder; LCSC Part # C138014
R11: 10m 1W 1%; R_1206_3216Metric_Pad1.30x1.75mm_HandSolder; LCSC Part # C7467248
U2: TLV70233_SOT23-5; SOT-23-5; LCSC Part # C26833
U3: INA219AxDCN; SOT-23-8; LCSC Part # C2155693

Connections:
+3V3: C2.1, C3.1, U2.5 (OUT), U3.4 (VS); also elsewhere on the board
+5V: C1.1, R2.2, R11.1, U2.1 (IN), U2.3 (EN), U3.2 (IN-); also elsewhere on the board
GND: C1.2, C2.2, C3.2, C5.2, C9.2, C10.2, D2.1 (K), J6.5, J6.6, R9.2, R10.2, U2.2 (GND), U3.3 (GND), U3.7 (A0), U3.8 (A1); also elsewhere on the board
unnamed: D2.2 (A), R2.1
unnamed: C5.1, J6.1, J6.2, R11.2, U3.1 (IN+)
unnamed: J6.3, R7.1
unnamed: J6.4, R8.1
PB8/I2C1_SCL: U3.5 (SCL); also elsewhere on the board
PB9/I2C1_SDA: U3.6 (SDA); also elsewhere on the board
PC0/ADC1_IN10: C9.1, R7.2, R9.1; also elsewhere on the board
PC2/ADC1_IN12: C10.1, R8.2, R10.1; also elsewhere on the board

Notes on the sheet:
5V Power Input
Note: Mainboard's regulator has a maximum input voltage of 5.5V
5V to 3.3V regulator 300mA
